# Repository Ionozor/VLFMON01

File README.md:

## VLF monitoring station

Monitoring station optimized for (Sudden ionospheric disturbances) SID monitoring and detection by monitoring of VLF signals from submarine transmitters.

## Hardware

### Antenna

The loop magnetic antenna is based on use of [VLFANT01 MLAB module](https://github.com/mlab-modules/VLFANT01).

## Additional possible uses

  * Lightning detection

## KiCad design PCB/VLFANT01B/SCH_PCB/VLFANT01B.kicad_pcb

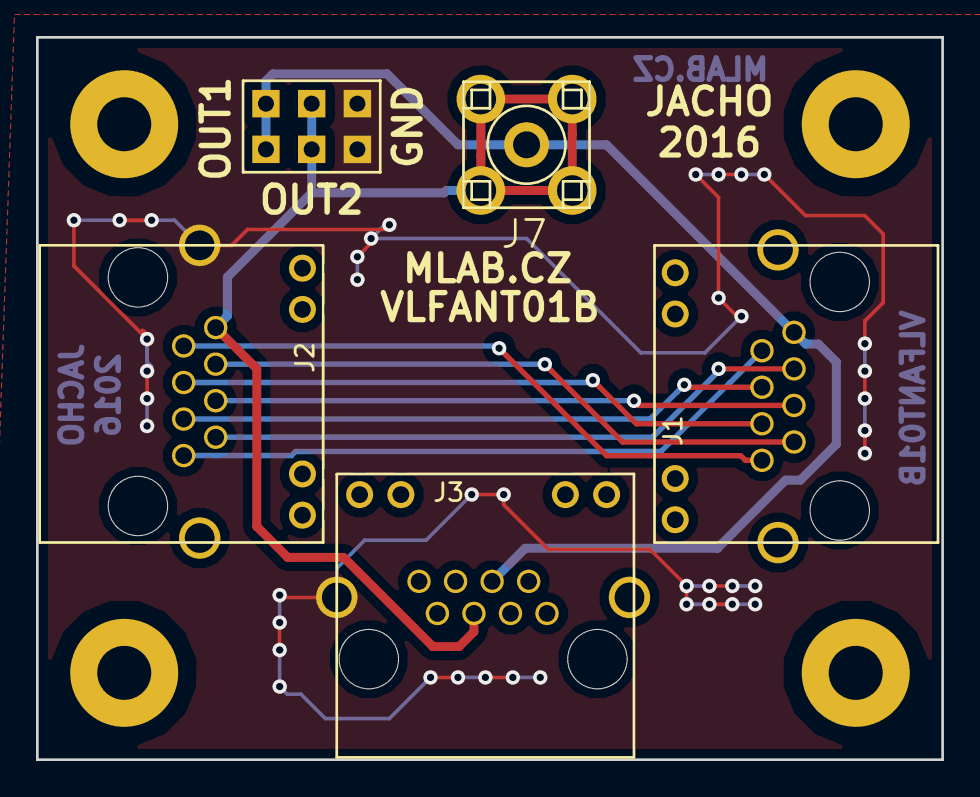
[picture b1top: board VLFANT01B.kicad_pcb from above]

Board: 2 copper layers, 50.3 x 40.1 mm, 9 parts (0 on the bottom side), 10 nets.

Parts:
J1, J2, J3: RJ45_RJHSE-5384; RJHSE-5384(RJ45)
J7: SMA; SMA6251A13G50
J9: JUMP_3X2; Straight_2x03
M1, M2, M3, M4: HOLE; MountingHole_3mm

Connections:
/OUT1: J1.1, J3.4, J7.1, J9.1, J9.2
/OUT2: J2.8, J3.5, J7.2, J9.3, J9.4
GND: J2.13, J3.13, J9.5, J9.6
unnamed: J1.2, J2.1
unnamed: J1.3, J2.2
unnamed: J1.4, J2.3
unnamed: J1.5, J2.4
unnamed: J1.6, J2.5
unnamed: J1.7, J2.6
unnamed: J1.8, J2.7

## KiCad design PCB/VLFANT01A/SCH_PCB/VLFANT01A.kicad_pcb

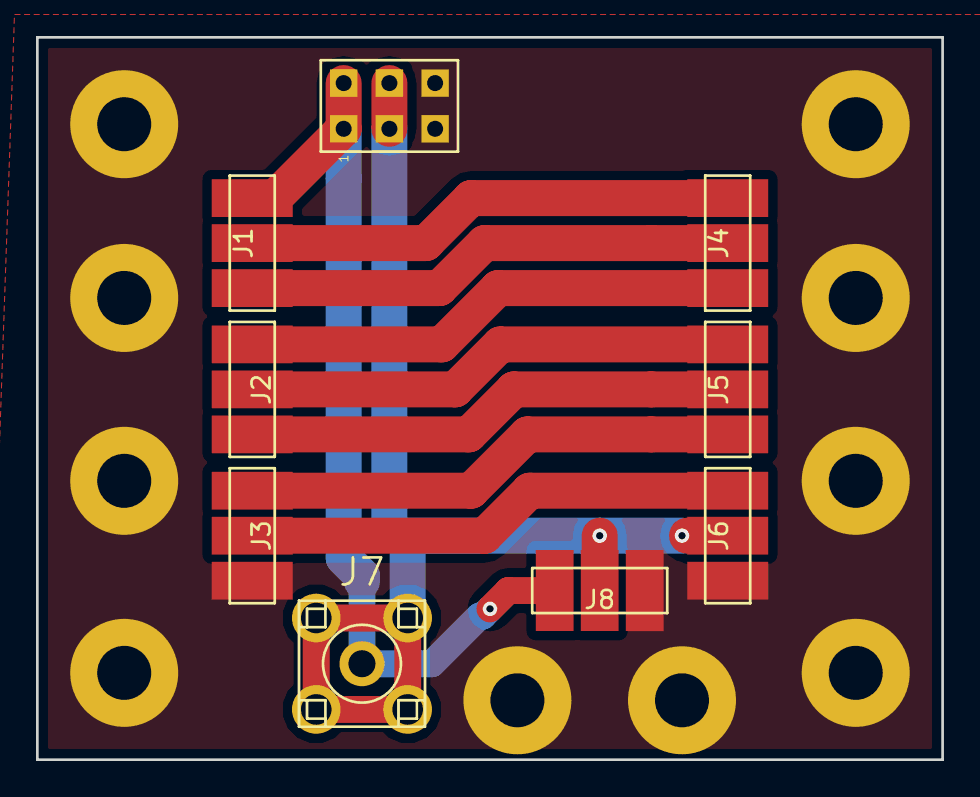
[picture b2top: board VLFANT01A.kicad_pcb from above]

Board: 2 copper layers, 50.3 x 40.1 mm, 19 parts (0 on the bottom side), 10 nets.

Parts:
J1, J2, J3, J4, J5, J6, J8: CONN_3; AVX_009175003001006
J7: SMA; SMA6251A13G50
J9: JUMP_3X2; Straight_2x03
M1, M2, M3, M4, M5, M6, M7, M8, M9, M10: HOLE; MountingHole_3mm

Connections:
/1: J1.2, J4.1
/2: J1.3, J4.2
/3: J2.3, J4.3
/4: J2.2, J5.1
/5: J2.1, J5.2
/6: J3.3, J5.3
/7: J3.2, J6.1
/OUT1: J1.1, J7.1, J8.1, J9.1, J9.2
/OUT2: J6.2, J7.2, J8.2, J9.3, J9.4
GND: J3.1, J6.3, J8.3, J9.5, J9.6, M1.1, M2.1, M3.1, M4.1, M5.1, M6.1, M7.1, M8.1, M9.1, M10.1

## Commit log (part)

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2016-09-04 upravy primo na testovacim odroidu aktualne nefungujici verze.
2016-09-04 Upravy ke zvyseni kvality testovani pri primem pripojeni SPI.
2016-09-04 kombinace zdrojovych kodu.
2016-09-05 oprava chyby s adresovanim slovniku.
2016-09-05 uprava kodu pro ovladani pres I2C.
2016-09-05 oprava importu.
2016-09-05 odstraneni vypisu.
2016-09-05 oprava vysky dilu radiaciniho situ pro lepsi tisknutelnost. A aktualizace parametru tisku.
2016-09-05 zmena krabicky
2016-09-05 zmena
2016-09-06 Fungujici kod s internim oscilatorem.
2016-09-06 zapnuty externi oscilator.
2016-09-06 finalni upravy kodu, odstraneni ladicich vypisu.
2016-09-06 upraveny rychlosti a vykony.
2016-09-07 zaznam potrebnych konstrukcnich vylepseni.
2016-09-07 aktualizace dokumentace.
2016-09-07 pridani identifikacniho textu do modelu podlozky.
2016-09-07 zamezeni resetu bez pouziti prikazu float.
2016-09-08 pridani noveho testu s vypisem statusu.
2016-09-08 zmena signalizacniho pinu vypadku napajeni.
2016-09-08 zmena nastaveni napeti na motoru.
    --Thisy
    line, and those below, will be ignored--
    M CLOCKMOT.py
2016-09-11 nastaven stejny smer pro vsechny rychlosti.
2016-09-12 pridani poznamek k plosnemu spoji.
2016-09-13 zalozeni modulu symetrizačniho transformatoru.
2016-09-13 pridani utlumoveho clanku na vstup symetrizacniho clenu.
2016-09-13 Zalozeninoveho modulu pro differencni SPI.
2016-09-13 smazani komponent, ktere jsou ve schema navic.
2016-09-14 Poznamka k osazovani rezistoru na vystupu modulu.
2016-09-14 aktualizace seznamu soucastek.
2016-09-15 pridani dalsich seriovych odporu pro zvyseni mozne impedance.
2016-09-15 Oprava cisla nozicky u jednotky B.
2016-09-15 zmena zapojeni tak aby bylo mozne modul pouzit jak jako master, tak i slave.
2016-09-15 pridani datasheetu.
2016-09-16 odstraneni linearniho stabilizatoru.
2016-09-16 naimportovani netlistu do PCB editoru.
2016-09-16 Vylepseni layoutu a potisku.
2016-09-16 pridani dalsich potencialnich obvodu pro RTC a pripadne srazkomer.
2016-09-16 vybran obvod pro RTC modul.
2016-09-17 pridani pauzy pred reset. uprava startovaciho skriptu tak, ze nemuze spustit vic procesu.
2016-09-17 snizena akcelarace motoru. zvyseny otacky na 37.5/min.
2016-09-17 zvetseni doby cekani na zastaveni motoru pred resetem.
2016-09-17 prodlouzena doba cekani na zastaveni motoru. k
2016-09-21 Pridan spousteci skript, ktery zabrani vicenasobnemu spusteni programu. Pridano ukonceni programu po spusteni vypinaciho procesu.
2016-09-21 oprava cesty
2016-09-21 pragram po sputeni ceka 30s na uplne nabehnuti napajeni a ostatnich programu, az po teto dobe je citlivy na vypadek napajeni.
2016-09-22 Doplneni popisku na PCB.
2016-09-22 vygenerovani QR kodu.
2016-09-23 pridani obrazku PHmetru.
2016-09-26 premisteni soucastek do lepsich pozic.
2016-09-26 zlepseni layoutu.
2016-09-27 zalozeni zarizeni pro mereni s prumyslovymi snimaci.
2016-09-27 doplnena možnost propojení přes UTP kabel.
2016-09-28 Zapis vylepseni.
2016-09-29 vygenerovani vyrobnich dat pro moduly pulsecatch.
2016-09-29 vygerovani vyrobnich dat.
2016-09-29 uprava rozmeru desky a pregenerovani technologickych vystupu.
2016-09-30 Dokumentace
2016-09-30 Navod
2016-10-04 pridani GSM modulu.
2016-10-09 Další film
2016-10-11 opravy chyb na breakoutframe pro odroid C1+
2016-10-19 zalozeni noveho breakoutframe pro RPi3
2016-10-19 doplneni textu oznacujiciho typ breakout frame.
2016-10-20 vygenerovani nahledu.
2016-10-25 smazani souboru po stare verzi.
2016-10-25 vytvoren breakoutframe pro Raspberry Pi3
2016-10-26 fix některých geometrických problémů..
2016-10-28 vylepseni vyrezu pro ethernet konektor
2016-10-28 pridani vyrezu na napajeci konektor.
2016-10-29 Version for mictowave owen transformator.
2016-10-30 Time adjustment
2016-11-02 Ondrovo mereni presnosti vstupu.
2016-11-06 zapiz nalezenych chyb u GSM modulu.
2016-11-07 novy program pro cteni snimacu na proudove smycce.
2016-11-07 pridani adres pro dalsi modul.
2016-11-08 Added demoversion for DRO.
2016-11-08 PCRD -> CANDY in DRO example
2016-11-11 urava layoutu u IO.
2016-11-13 vylepšení layoutu.
2016-11-13 uprava pcb a henerovani vyrobnich dat
2016-11-13 pridani dokumentace ke GSM modulu.
2016-11-23 aktualizace faviconu podle aktualniho grafickeho stylu.
2016-11-30 pregenerovani vyrobnich STL podle zdrojoveho kodu.
2016-12-01 pridani ukladani do souboru.
2016-12-01 pridani externiho souboru s konfiguraci.
2016-12-02 Nova data
2016-12-02 uprava formatu vystupu.
2016-12-09 Nový univerzální modul pro pásmové filtry.
2016-12-09 Doplneneni projektoveho souboru s navrhem filtru.
2016-12-11 aktualizace označení součástek.
2016-12-13 odstraneni jednoho stupne filtru.
2016-12-13 opraveny hodnoty soucastek.
2016-12-14 pridani fotodokumentace z rozebraneho monitoru dechu.
2016-12-20 BP01B PCB upravy, WINDGAUGE02A upravy
2016-12-22 rj12v01a novy modul
2016-12-23 zmena drzaku
2016-12-23 furt to na me kricelo, tak jsem to potvrdil.
2016-12-23 uprava modelu
2016-12-30 Zalozeni noveho projektu merice vykonu a pridani zapomenutych dokumentacnich soboru.
2017-01-09 aktualizace obrazku.
2017-01-09 pridani modelu pouziteho jako kryt pro displej.
2017-01-10 pridani noveho pristroje pro laboratorni mereni vykonu.
2017-01-10 pridani fotografie prototypu mericiho pristroje vykonu.
2017-01-12 Pridani dokumentacnich obrazku a smazani slozky s Moduly kvuli presunu na Github: https://github.com/MLAB-project/Modules
2017-01-12 pridan skript pro aktualizaci repozitare Modules z githubu.
2017-01-12 aktualizovano logo, odstranen odkaz na WebSVN a nahrazen odkazem na GitHub.
2017-01-14 vytvoreni noveho citace
2017-01-25 Fotky pro meteostanici
2017-02-07 Pismo zmeneno na vystoupnute. Pridan prechod mezi vertikalni a horizontalni casti drzaku.
2017-02-08 vytvoreni novych zarizeni
2017-02-17 Pridani navrhu podlozky pro podlozeni plastovych krabic s prevodniky.
2017-02-20 foto
2017-04-03 Presunuti dokumentace phmetru na github. https://github.com/ODZ-UJF-AV-CR/pHmeter
2017-05-24 CELICKA NA KRABICKU
2017-05-24 uprava celicek
2017-05-31 Novy detektor atmosferickych jevu.
2017-06-04 gcode for box
2019-09-11 Moving of VLFANT module in to standard MLAB modules repository.
2021-07-17 Improve documentation.
2021-07-17 Improve photo quality.
